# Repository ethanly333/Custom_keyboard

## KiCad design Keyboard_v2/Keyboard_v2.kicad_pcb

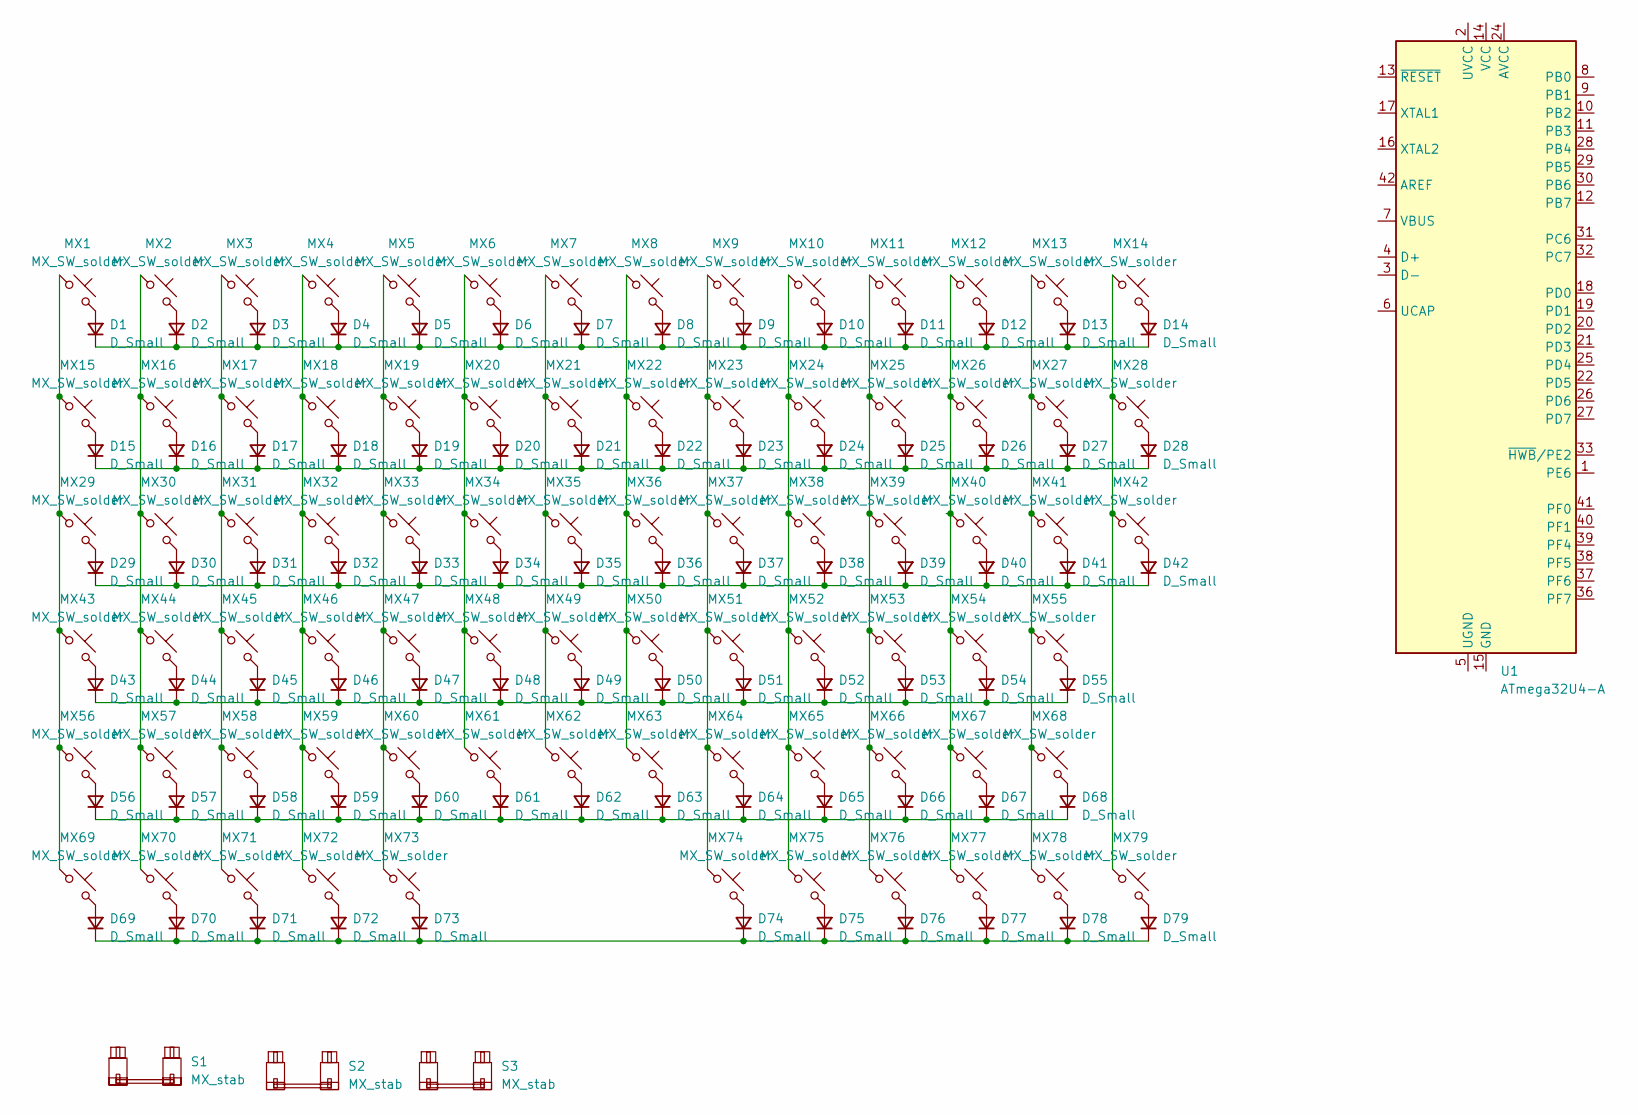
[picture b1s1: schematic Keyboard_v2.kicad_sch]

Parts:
D1, D2, D3, D4, D5, D6, D7, D8, D9, D10, D11, D12, D13, D14, D15, D16, D17, D18, D19, D20, D21, D22, D23, D24, D25, D26, D27, D28, D29, D30, D31, D32, D33, D34, D35, D36, D37, D38, D39, D40, D41, D42, D43, D44, D45, D46, D47, D48, D49, D50, D51, D52, D53, D54, D55, D56, D57, D58, D59, D60, D61, D62, D63, D64, D65, D66, D67, D68, D69, D70, D71, D72, D73, D74, D75, D76, D77, D78, D79: D_Small; D_SOD-123
MX1, MX28, MX29: MX_SW_solder; SW_MX_1.5u
MX2, MX3, MX4, MX5, MX6, MX7, MX8, MX9, MX10, MX11, MX12, MX13, MX14, MX15, MX16, MX17, MX18, MX19, MX20, MX21, MX22, MX23, MX24, MX25, MX26, MX27, MX30, MX31, MX32, MX33, MX34, MX35, MX36, MX37, MX38, MX39, MX40, MX41, MX42, MX44, MX45, MX46, MX47, MX48, MX49, MX50, MX51, MX52, MX53, MX54, MX56, MX57, MX58, MX59, MX60, MX61, MX62, MX63, MX64, MX65, MX66, MX67, MX68, MX69, MX70, MX71, MX73, MX75, MX76, MX77, MX78, MX79: MX_SW_solder; SW_MX_1u
MX43, MX55: MX_SW_solder; SW_MX_1.75u
MX72, MX74: MX_SW_solder; SW_MX_1.25u
S1, S2: MX_stab; STAB_MX_P_2.25u
S3: MX_stab; STAB_MX_P_6u
U1: ATmega32U4-A; TQFP-44_10x10mm_P0.8mm

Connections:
unnamed: D1.2 (A), MX1.2
unnamed: D1.1 (K), D2.1 (K), D3.1 (K), D4.1 (K), D5.1 (K), D6.1 (K), D7.1 (K), D8.1 (K), D9.1 (K), D10.1 (K), D11.1 (K), D12.1 (K), D13.1 (K), D14.1 (K)
unnamed: D2.2 (A), MX2.2
unnamed: D3.2 (A), MX3.2
unnamed: D4.2 (A), MX4.2
unnamed: D5.2 (A), MX5.2
unnamed: D6.2 (A), MX6.2
unnamed: D7.2 (A), MX7.2
unnamed: D8.2 (A), MX8.2
unnamed: D9.2 (A), MX9.2
unnamed: D10.2 (A), MX10.2
unnamed: D11.2 (A), MX11.2
unnamed: D12.2 (A), MX12.2
unnamed: D13.2 (A), MX13.2
unnamed: D14.2 (A), MX14.2
unnamed: D15.2 (A), MX15.2
unnamed: D15.1 (K), D16.1 (K), D17.1 (K), D18.1 (K), D19.1 (K), D20.1 (K), D21.1 (K), D22.1 (K), D23.1 (K), D24.1 (K), D25.1 (K), D26.1 (K), D27.1 (K), D28.1 (K)
unnamed: D16.2 (A), MX16.2
unnamed: D17.2 (A), MX17.2
unnamed: D18.2 (A), MX18.2
unnamed: D19.2 (A), MX19.2
unnamed: D20.2 (A), MX20.2
unnamed: D21.2 (A), MX21.2
unnamed: D22.2 (A), MX22.2
unnamed: D23.2 (A), MX23.2
unnamed: D24.2 (A), MX24.2
unnamed: D25.2 (A), MX25.2
unnamed: D26.2 (A), MX26.2
unnamed: D27.2 (A), MX27.2
unnamed: D28.2 (A), MX28.2
unnamed: D29.2 (A), MX29.2
unnamed: D29.1 (K), D30.1 (K), D31.1 (K), D32.1 (K), D33.1 (K), D34.1 (K), D35.1 (K), D36.1 (K), D37.1 (K), D38.1 (K), D39.1 (K), D40.1 (K), D41.1 (K), D42.1 (K)
unnamed: D30.2 (A), MX30.2
unnamed: D31.2 (A), MX31.2
unnamed: D32.2 (A), MX32.2
unnamed: D33.2 (A), MX33.2
unnamed: D34.2 (A), MX34.2
unnamed: D35.2 (A), MX35.2
unnamed: D36.2 (A), MX36.2
unnamed: D37.2 (A), MX37.2
unnamed: D38.2 (A), MX38.2
unnamed: D39.2 (A), MX39.2
unnamed: D40.2 (A), MX40.2
unnamed: D41.2 (A), MX41.2
unnamed: D42.2 (A), MX42.2
unnamed: D43.2 (A), MX43.2
unnamed: D43.1 (K), D44.1 (K), D45.1 (K), D46.1 (K), D47.1 (K), D48.1 (K), D49.1 (K), D50.1 (K), D51.1 (K), D52.1 (K), D53.1 (K), D54.1 (K), D55.1 (K)
unnamed: D44.2 (A), MX44.2
unnamed: D45.2 (A), MX45.2
unnamed: D46.2 (A), MX46.2
unnamed: D47.2 (A), MX47.2
unnamed: D48.2 (A), MX48.2
unnamed: D49.2 (A), MX49.2
unnamed: D50.2 (A), MX50.2
unnamed: D51.2 (A), MX51.2
unnamed: D52.2 (A), MX52.2
unnamed: D53.2 (A), MX53.2
unnamed: D54.2 (A), MX54.2
unnamed: D55.2 (A), MX55.2
unnamed: D56.2 (A), MX56.2
unnamed: D56.1 (K), D57.1 (K), D58.1 (K), D59.1 (K), D60.1 (K), D61.1 (K), D62.1 (K), D63.1 (K), D64.1 (K), D65.1 (K), D66.1 (K), D67.1 (K), D68.1 (K)
unnamed: D57.2 (A), MX57.2
unnamed: D58.2 (A), MX58.2
unnamed: D59.2 (A), MX59.2
unnamed: D60.2 (A), MX60.2
unnamed: D61.2 (A), MX61.2
unnamed: D62.2 (A), MX62.2
unnamed: D63.2 (A), MX63.2
unnamed: D64.2 (A), MX64.2
unnamed: D65.2 (A), MX65.2
unnamed: D66.2 (A), MX66.2
unnamed: D67.2 (A), MX67.2
unnamed: D68.2 (A), MX68.2
unnamed: D69.2 (A), MX69.2
unnamed: D69.1 (K), D70.1 (K), D71.1 (K), D72.1 (K), D73.1 (K), D74.1 (K), D75.1 (K), D76.1 (K), D77.1 (K), D78.1 (K), D79.1 (K)
unnamed: D70.2 (A), MX70.2
unnamed: D71.2 (A), MX71.2
unnamed: D72.2 (A), MX72.2
unnamed: D73.2 (A), MX73.2
unnamed: D74.2 (A), MX74.2
unnamed: D75.2 (A), MX75.2
unnamed: D76.2 (A), MX76.2
unnamed: D77.2 (A), MX77.2
unnamed: D78.2 (A), MX78.2
unnamed: D79.2 (A), MX79.2
unnamed: MX1.1, MX15.1, MX29.1, MX43.1, MX56.1, MX69.1
unnamed: MX10.1, MX24.1, MX38.1, MX52.1, MX65.1, MX75.1
unnamed: MX11.1, MX25.1, MX39.1, MX53.1, MX66.1, MX76.1
unnamed: MX12.1, MX26.1, MX40.1, MX54.1, MX67.1, MX77.1
unnamed: MX13.1, MX27.1, MX41.1, MX55.1, MX68.1, MX78.1
unnamed: MX14.1, MX28.1, MX42.1, MX79.1
unnamed: MX2.1, MX16.1, MX30.1, MX44.1, MX57.1, MX70.1
unnamed: MX3.1, MX17.1, MX31.1, MX45.1, MX58.1, MX71.1
unnamed: MX4.1, MX18.1, MX32.1, MX46.1, MX59.1, MX72.1
unnamed: MX5.1, MX19.1, MX33.1, MX47.1, MX60.1, MX73.1
unnamed: MX6.1, MX20.1, MX34.1, MX48.1, MX61.1
unnamed: MX7.1, MX21.1, MX35.1, MX49.1, MX62.1
unnamed: MX8.1, MX22.1, MX36.1, MX50.1, MX63.1
unnamed: MX9.1, MX23.1, MX37.1, MX51.1, MX64.1, MX74.1

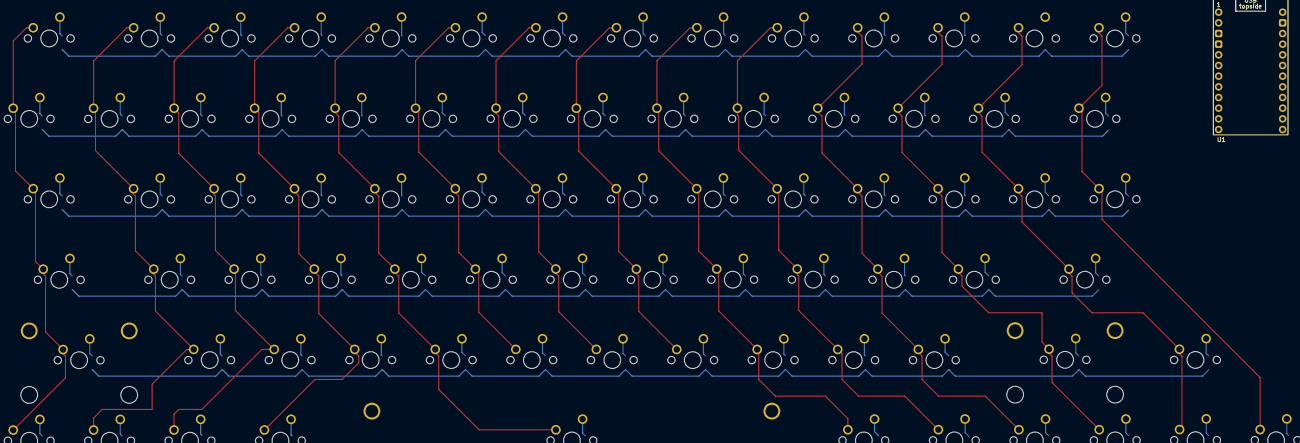
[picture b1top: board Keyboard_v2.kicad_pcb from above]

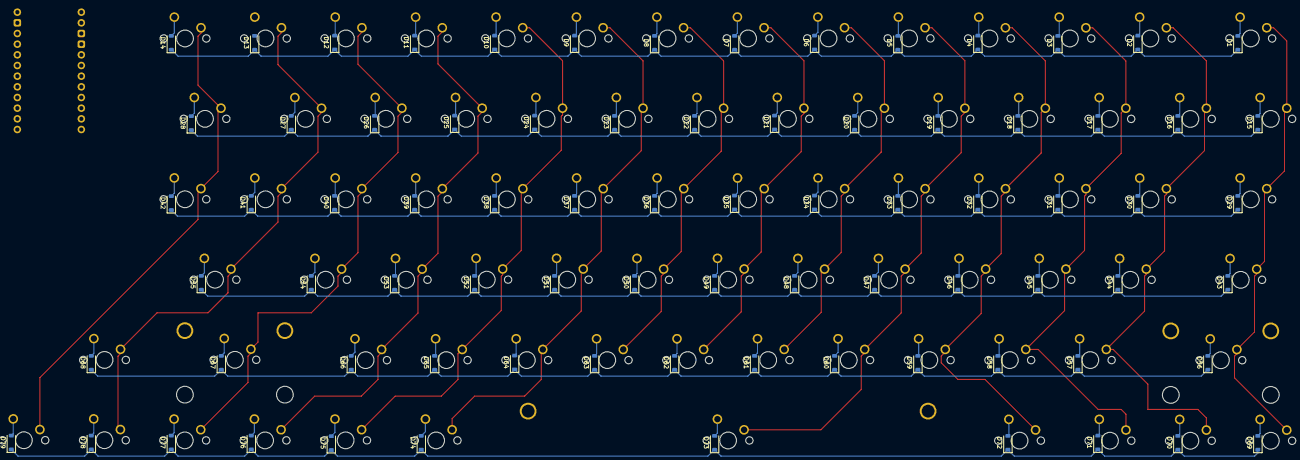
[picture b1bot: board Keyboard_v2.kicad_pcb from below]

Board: 2 copper layers, 162 parts (79 on the bottom side), 99 nets.

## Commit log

2023-06-11 initial commmit
2023-06-11 add submodules
2023-06-11 add libraries and footprints
2023-06-11 MCU schematic
2023-06-11 added sketch for plate
2023-06-11 added switch matrix and component footprints
2023-06-12 pcb laid out - need to check hole placements
2023-06-12 routed MCU and key rows
2023-06-14 all rows and cols connected to MCU
2023-06-14 add ground fills
2023-06-21 init commit for v2
2023-06-22 key matrix done. placing pcb now
2023-06-22 all keys routed
2023-06-22 pcb is routed and ground fills added
